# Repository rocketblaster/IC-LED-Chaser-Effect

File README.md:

# LED Chaser Effect PCB

This is an LED chaser effect with a custom shaped PCB edge cut of a flower. It uses NE555 and CD4017 integrated circuits to achieve this effect. I made this because I want to experiment with integrated circuits and create an LED that lights up in a pattern or so through these chips.

How this will work is the LEDs will light up in a pattern and basically feel like it is chasing something bouncing back and forth. Because the 4017 counts from Q0-9 it will turn on a specific LED and the way I placed it, the LEDs look like they're chasing each other in random directions.

---
## Schematic

## PCB

---

Inspired by the various circular LED chaser circuits

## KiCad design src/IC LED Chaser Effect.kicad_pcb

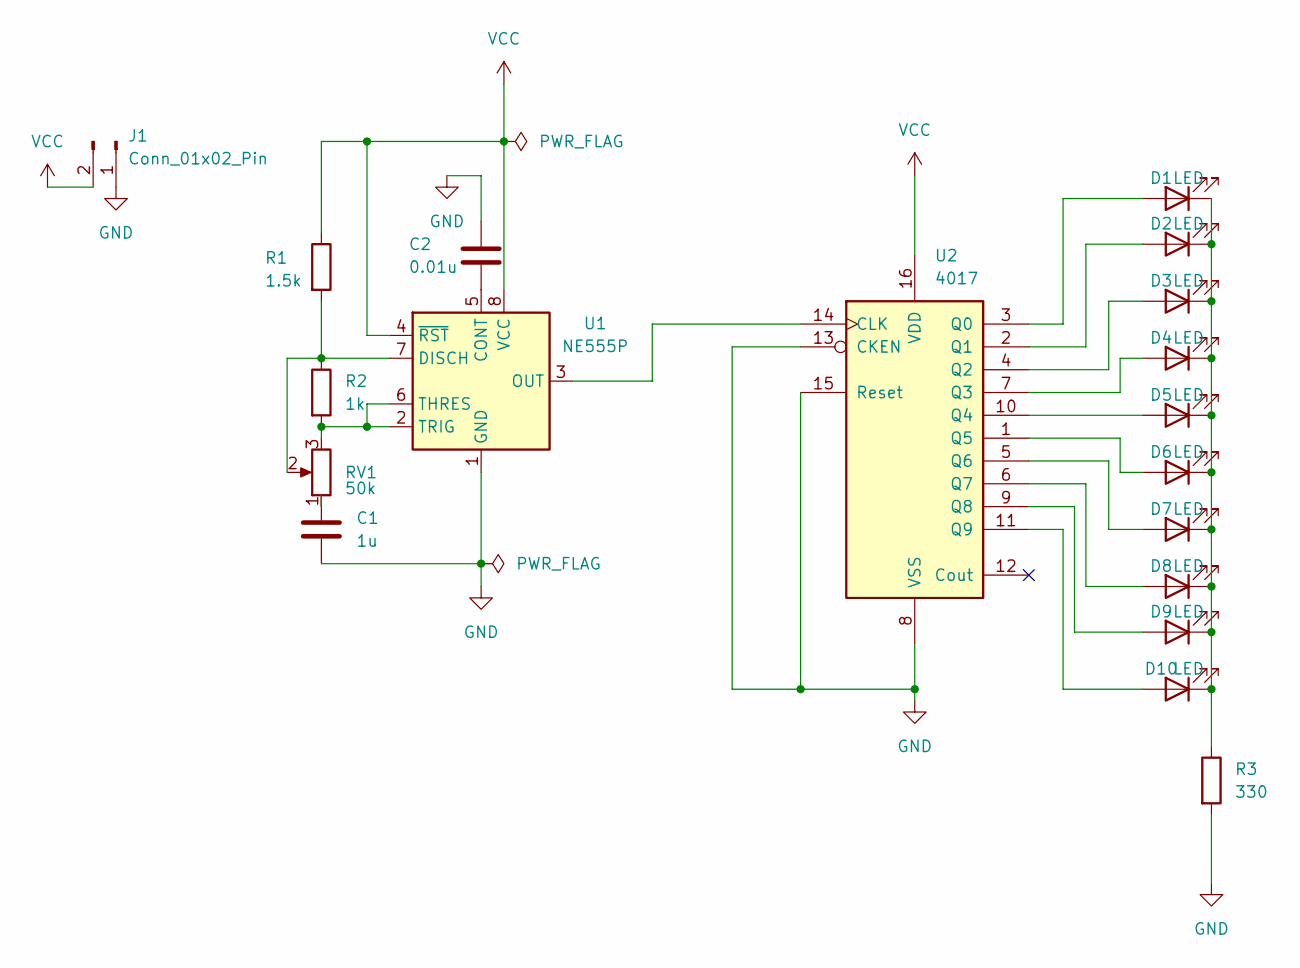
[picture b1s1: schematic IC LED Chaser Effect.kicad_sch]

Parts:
C1: 1u; C_Disc_D5.0mm_W2.5mm_P5.00mm
C2: 0.01u; C_Disc_D5.0mm_W2.5mm_P5.00mm
D1, D2, D3, D4, D5, D6, D7, D8, D9, D10: LED; LED_D5.0mm
J1: Conn_01x02_Pin; PinHeader_1x02_P2.54mm_Vertical
R1: 1.5k; R_Axial_DIN0207_L6.3mm_D2.5mm_P7.62mm_Horizontal
R2: 1k; R_Axial_DIN0207_L6.3mm_D2.5mm_P7.62mm_Horizontal
R3: 330; R_Axial_DIN0207_L6.3mm_D2.5mm_P7.62mm_Horizontal
RV1: 50k; Potentiometer_Vishay_T93YA_Vertical
U1: NE555P; DIP-8_W7.62mm
U2: 4017; DIP-16_W7.62mm

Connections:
GND: C1.2, C2.1, J1.1, R3.2, U1.1 (GND), U2.8 (VSS), U2.13 (CKEN), U2.15 (Reset)
unnamed: C1.1, RV1.1
unnamed: D1.2 (A), U2.3 (Q0)
unnamed: D1.1 (K), D2.1 (K), D3.1 (K), D4.1 (K), D5.1 (K), D6.1 (K), D7.1 (K), D8.1 (K), D9.1 (K), D10.1 (K), R3.1
unnamed: D2.2 (A), U2.2 (Q1)
unnamed: D3.2 (A), U2.4 (Q2)
unnamed: D4.2 (A), U2.7 (Q3)
unnamed: D5.2 (A), U2.10 (Q4)
unnamed: D6.2 (A), U2.1 (Q5)
unnamed: D7.2 (A), U2.5 (Q6)
unnamed: D8.2 (A), U2.6 (Q7)
unnamed: D9.2 (A), U2.9 (Q8)
unnamed: D10.2 (A), U2.11 (Q9)
unnamed: C2.2, U1.5 (CONT)
unnamed: R1.2, R2.1, RV1.2, U1.7 (DISCH)
unnamed: U1.3 (OUT), U2.14 (CLK)
unnamed: R2.2, RV1.3, U1.2 (TRIG), U1.6 (THRES)
VCC: J1.2, R1.1, U1.4 (~RST), U1.8 (VCC), U2.16 (VDD)

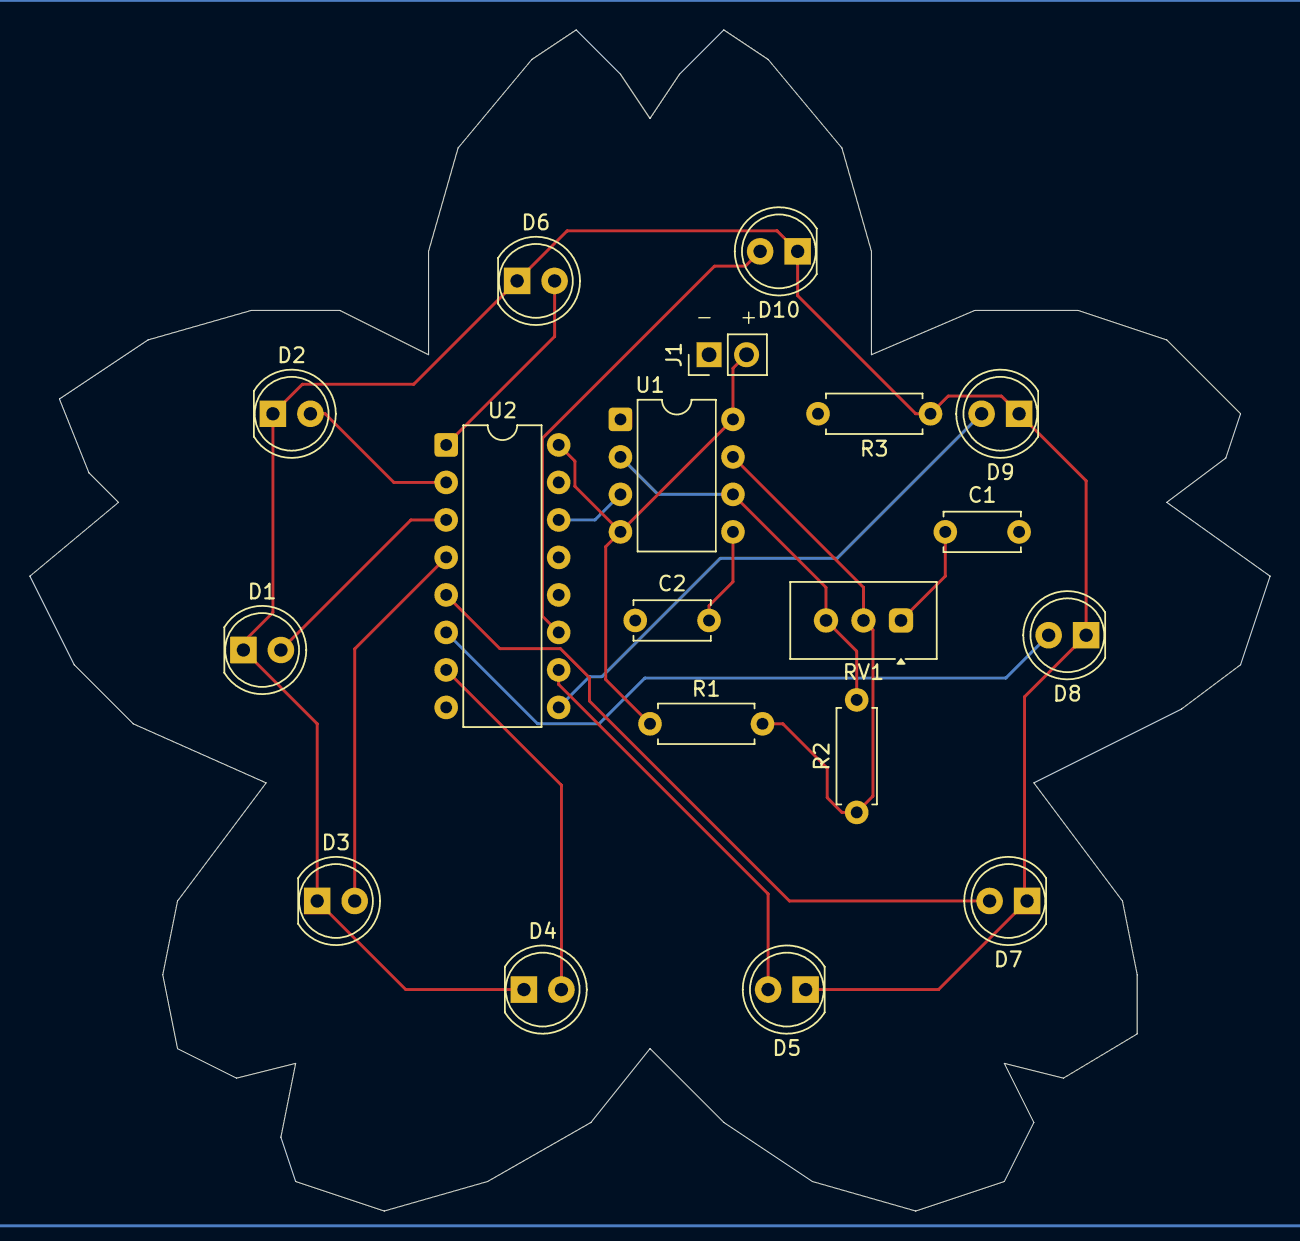
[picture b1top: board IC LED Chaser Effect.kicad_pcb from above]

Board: 2 copper layers, 84.0 x 80.0 mm, 19 parts (0 on the bottom side), 18 nets.

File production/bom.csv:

Designator,Footprint,Quantity,Value,LCSC Part #
C1,C_Disc_D5.0mm_W2.5mm_P5.00mm,1,1u,
C2,C_Disc_D5.0mm_W2.5mm_P5.00mm,1,0.01u,
"D1, D10, D2, D3, D4, D5, D6, D7, D8, D9",LED_D5.0mm,10,LED,
J1,PinHeader_1x02_P2.54mm_Vertical,1,Conn_01x02_Pin,
R1,R_Axial_DIN0207_L6.3mm_D2.5mm_P7.62mm_Horizontal,1,1.5k,
R2,R_Axial_DIN0207_L6.3mm_D2.5mm_P7.62mm_Horizontal,1,1k,
R3,R_Axial_DIN0207_L6.3mm_D2.5mm_P7.62mm_Horizontal,1,330,
RV1,Potentiometer_Vishay_T93YA_Vertical,1,50k,
U1,DIP-8_W7.62mm,1,NE555P,
U2,DIP-16_W7.62mm,1,4017,

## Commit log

2026-03-31 Created attachments
2026-03-31 Added image
2026-03-31 Updated journal.md
2026-04-01 Update Journal
2026-04-01 Upload image
2026-04-01 Moved image
2026-04-01 Update image
2026-04-01 Updated image
2026-04-01 Upload image9
2026-04-01 Updated Journal
2026-04-01 Upload image10
2026-04-02 Upload image11
2026-04-02 Upload image12
2026-04-02 Moved image12
2026-04-03 Upload image14
2026-04-03 Uplaod image18
2026-04-03 Upload image19
2026-04-03 Upload image20
2026-04-03 Upload image21
2026-04-03 Upload image22
2026-04-03 Update PCB image
2026-04-03 Upload image24
2026-04-03 Upload image25
2026-04-03 Update read me desc
2026-04-03 Upload src files
2026-04-03 Upload production files
2026-04-03 Upload file
2026-06-08 Update production file
